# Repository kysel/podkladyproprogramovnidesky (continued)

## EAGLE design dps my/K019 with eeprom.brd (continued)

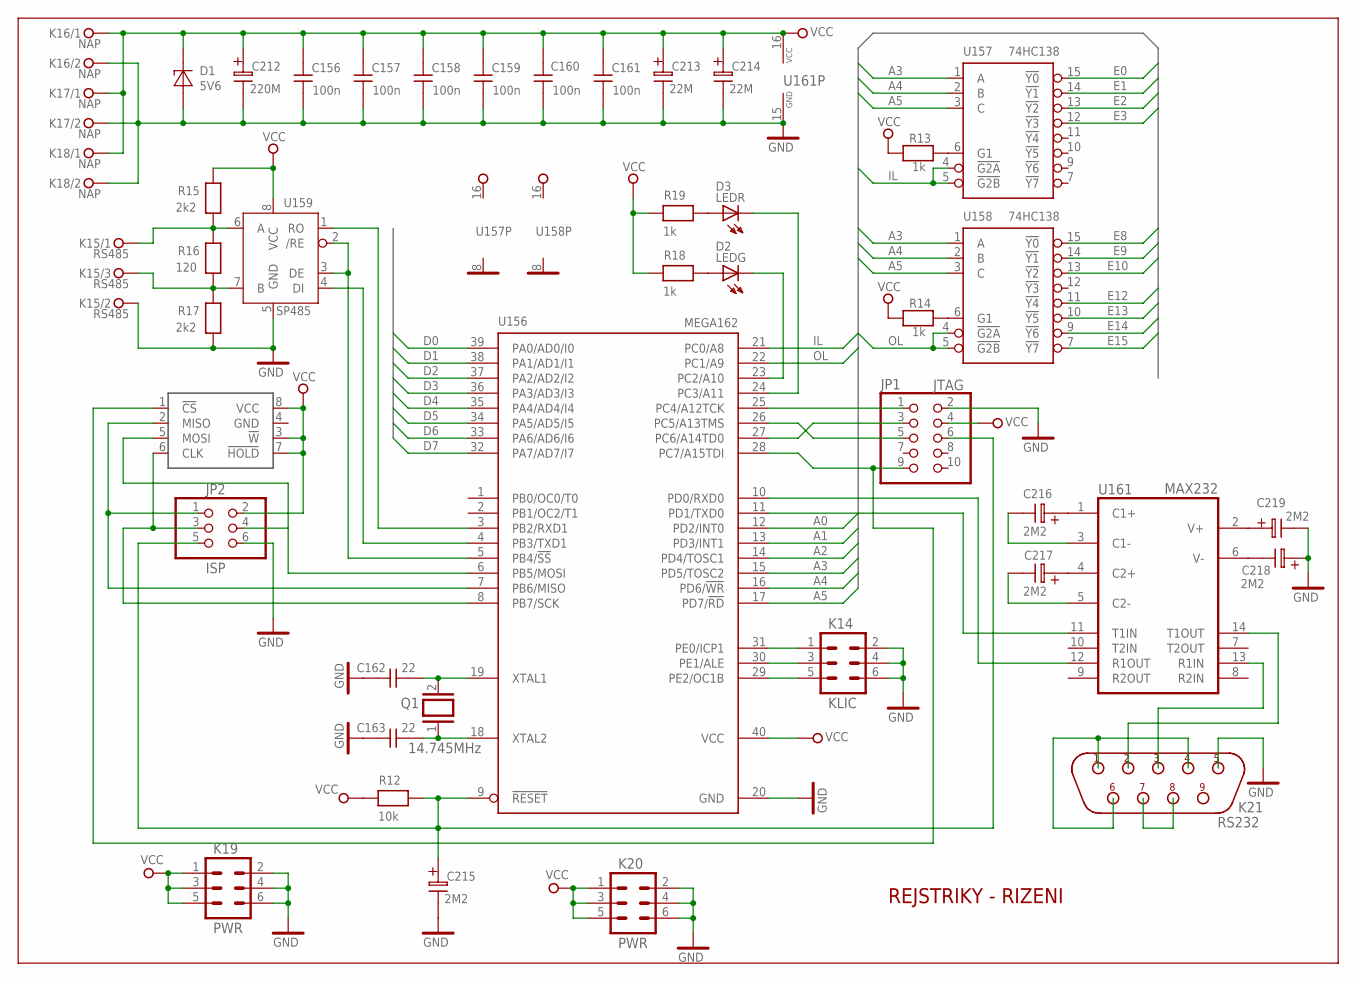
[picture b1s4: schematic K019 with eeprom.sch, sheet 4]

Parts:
C156, C157, C158, C159, C160, C161: 100n; C-5-2X8
C162, C163: 22; C-5-2X8
C212: 220M; EC-5
C213, C214: 22M; EC-2/5
C215, C216, C217, C218, C219: 2M2; EC-2/5
D1: 5V6; D-10
D2: LEDG; LED3
D3: LEDR; LED3
JP1: JTAG; 2X05
JP2: ISP; 2X03
K14: KLIC; ML6
K15: PSH02-03W; PSH02-03
K16, K17, K18: PSH02-02W; PSH02-02
K19, K20: PWR; ML06
K21: RS232; D-09F/90
Q1: 14.745MHz; QS
R12: 10k; R-7,5
R13, R14, R18, R19: 1k; R-7,5
R15, R17: 2k2; R-7,5
R16: 120; R-7,5
U156: MEGA162; DIL40
U157, U158: 74HC138; DIL16
U159: SP485; DIL-08
U161: MAX232; DIL16@2
U$389: M95XXSO; SO08

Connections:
A0: U156.12 (PD2/INT0); also elsewhere on the board
A1: U156.13 (PD3/INT1); also elsewhere on the board
A2: U156.14 (PD4/TOSC1); also elsewhere on the board
A3: U156.15 (PD5/TOSC2), U157.1 (A), U158.1 (A)
A4: U156.16 (PD6/!WR), U157.2 (B), U158.2 (B)
A5: U156.17 (PD7/!RD), U157.3 (C), U158.3 (C)
D0: U156.39 (PA0/AD0/I0); also elsewhere on the board
D1: U156.38 (PA1/AD1/I1); also elsewhere on the board
D2: U156.37 (PA2/AD2/I2); also elsewhere on the board
D3: U156.36 (PA3/AD3/I3); also elsewhere on the board
D4: U156.35 (PA4/AD4/I4); also elsewhere on the board
D5: U156.34 (PA5/AD5/I5); also elsewhere on the board
D6: U156.33 (PA6/AD6/I6); also elsewhere on the board
D7: U156.32 (PA7/AD7/I7); also elsewhere on the board
E0: U157.15 (!Y0); also elsewhere on the board
E1: U157.14 (!Y1); also elsewhere on the board
E2: U157.13 (!Y2); also elsewhere on the board
E3: U157.12 (!Y3); also elsewhere on the board
E8: U158.15 (!Y0); also elsewhere on the board
E9: U158.14 (!Y1); also elsewhere on the board
E10: U158.13 (!Y2); also elsewhere on the board
E12: U158.11 (!Y4); also elsewhere on the board
E13: U158.10 (!Y5); also elsewhere on the board
E14: U158.9 (!Y6); also elsewhere on the board
E15: U158.7 (!Y7); also elsewhere on the board
GND: C156.1, C157.1, C158.1, C159.1, C160.1, C161.1, C162.1, C163.1, C212.1, C213.1, C214.1, C215.1, C218.2, C219.1, D1.2 (A), JP1.2, JP2.6, K14.2, K14.4, K14.6, K15.2, K16.2, K17.2, K18.2, K19.2, K19.4, K19.6, K20.2, K20.4, K20.6, K21.5, R17.1, U156.20 (GND), U157.8 (GND), U158.8 (GND), U159.5 (GND), U161.15 (GND); also elsewhere on the board
IL: U156.21 (PC0/A8), U157.4 (!G2A), U157.5 (!G2B); also elsewhere on the board
unnamed: C162.2, Q1.2, U156.19 (XTAL1)
unnamed: C163.2, Q1.1, U156.18 (XTAL2)
unnamed: C215.2, JP1.6, JP2.5, R12.2, U156.9 (!RESET)
unnamed: K14.1, U156.31 (PE0/ICP1)
unnamed: K14.3, U156.30 (PE1/ALE)
unnamed: K14.5, U156.29 (PE2/OC1B)
unnamed: JP1.1, U156.25 (PC4/A12TCK)
unnamed: R13.2, U157.6 (G1)
unnamed: R14.2, U158.6 (G1)
unnamed: JP1.3, U156.27 (PC6/A14TD0)
unnamed: JP1.5, U156.26 (PC5/A13TMS)
unnamed: K15.1, R15.1, R16.2, U159.6 (A)
unnamed: K21.3, U161.13 (R1IN)
unnamed: JP1.9, U156.28 (PC7/A15TDI), U$389.1 (!CS)
unnamed: JP2.4, U156.6 (PB5/MOSI), U$389.5 (MOSI)
unnamed: JP2.1, U156.7 (PB6/MISO), U$389.2 (MISO)
unnamed: JP2.3, U156.8 (PB7/SCK), U$389.6 (CLK)
unnamed: U156.3 (PB2/RXD1), U159.1 (RO)
unnamed: U156.4 (PB3/TXD1), U159.4 (DI)
unnamed: U156.5 (PB4/!SS), U159.2 (/RE), U159.3 (DE)
unnamed: K21.1, K21.4, K21.6
unnamed: K15.3, R16.1, R17.2, U159.7 (B)
unnamed: K21.7, K21.8
unnamed: U156.10 (PD0/RXD0), U161.12 (R1OUT)
unnamed: U156.11 (PD1/TXD0), U161.11 (T1IN)
unnamed: C216.2, U161.1 (C1+)
unnamed: C217.2, U161.4 (C2+)
unnamed: C219.2, U161.2 (V+)
unnamed: C216.1, U161.3 (C1-)
unnamed: C217.1, U161.5 (C2-)
unnamed: C218.1, U161.6 (V-)
unnamed: D2.A, R18.2
unnamed: D3.A, R19.2
unnamed: K21.2, U161.14 (T1OUT)
unnamed: D2.K, U156.23 (PC2/A10)
unnamed: D3.K, U156.24 (PC3/A11)
OL: U156.22 (PC1/A9), U158.4 (!G2A), U158.5 (!G2B)
VCC: C156.2, C157.2, C158.2, C159.2, C160.2, C161.2, C212.2, C213.2, C214.2, D1.1 (K), JP1.4, JP2.2, K16.1, K17.1, K18.1, K19.1, K19.3, K19.5, K20.1, K20.3, K20.5, R12.1, R13.1, R14.1, R15.2, R18.1, R19.1, U156.40 (VCC), U157.16 (VCC), U158.16 (VCC), U159.8 (VCC), U161.16 (VCC), U$389.3 (!W), U$389.7 (!HOLD), U$389.8 (VCC); also elsewhere on the board

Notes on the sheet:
REJSTRIKY - RIZENI
RS485
NAP

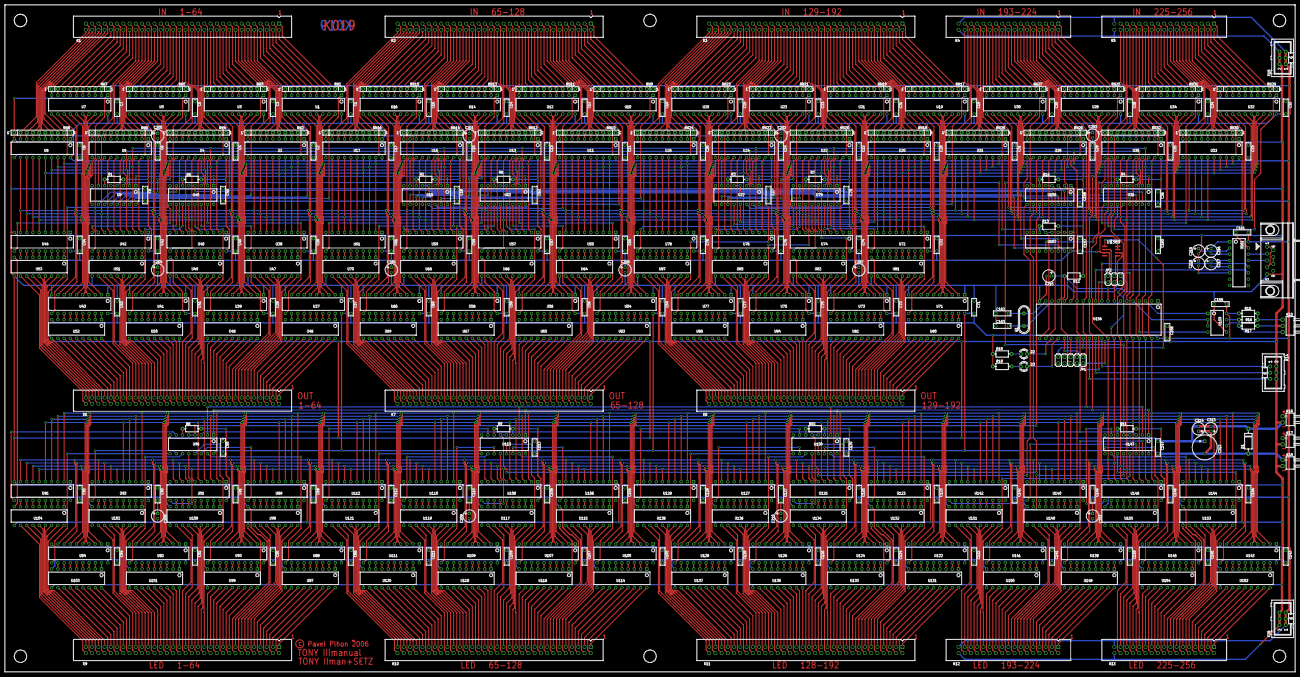
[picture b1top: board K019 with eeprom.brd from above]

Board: 2 copper layers, 525.8 x 271.8 mm, 366 parts (0 on the bottom side), 1316 nets.

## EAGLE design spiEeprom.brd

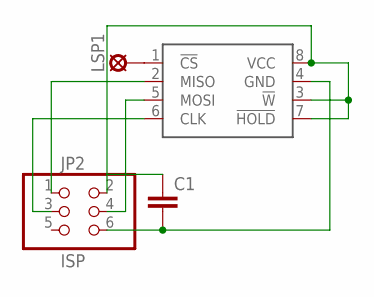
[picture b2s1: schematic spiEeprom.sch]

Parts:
C1: C-EUC0603; C0603
JP2: ISP; 2X03
LSP1: LSP10
U$1: M95XXSO; SO08

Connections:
CLK: JP2.3, U$1.6 (CLK)
GND: C1.2, JP2.6, U$1.4 (GND)
MISO: JP2.1, U$1.2 (MISO)
MOSI: JP2.4, U$1.5 (MOSI)
unnamed: LSP1.MP, U$1.1 (!CS)
VCC: C1.1, JP2.2, U$1.3 (!W), U$1.7 (!HOLD), U$1.8 (VCC)

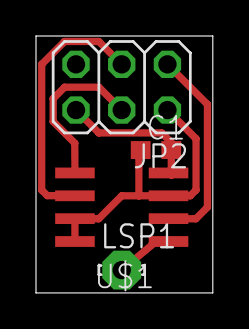
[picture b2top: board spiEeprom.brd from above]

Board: 2 copper layers, 9.8 x 14.3 mm, 4 parts (0 on the bottom side), 6 nets.

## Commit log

2013-08-27 initial
2013-08-31 zaloha
2013-09-01 1st release
2013-10-13 změna čísel IO
2013-10-17 install ..
